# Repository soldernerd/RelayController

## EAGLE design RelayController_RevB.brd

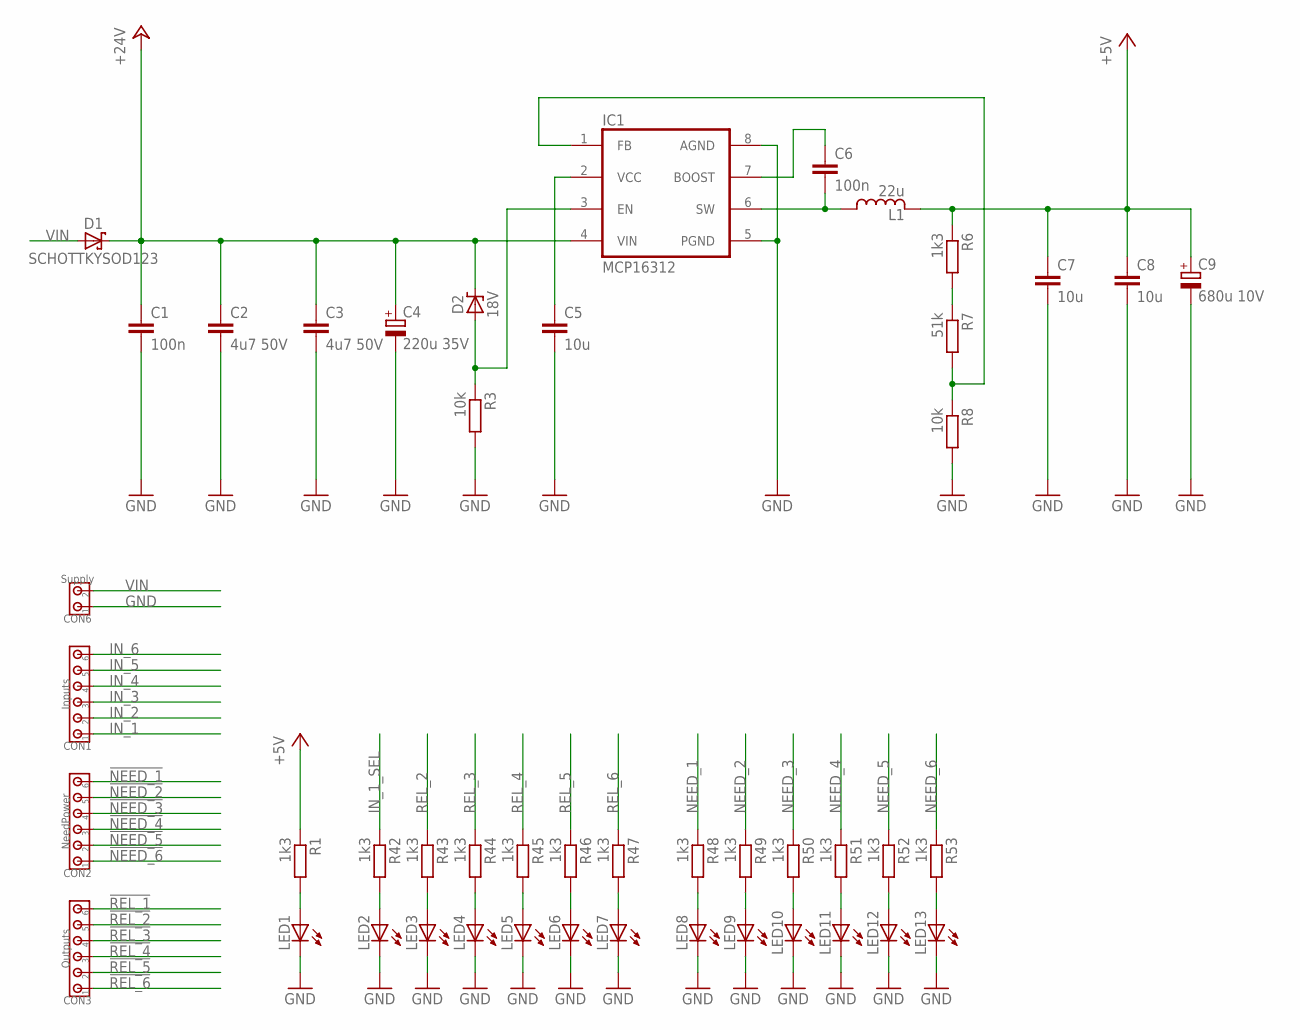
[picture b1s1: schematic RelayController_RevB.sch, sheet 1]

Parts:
C1, C6: 100n; C0805
C2, C3: 4u7 50V; C1206
C4: 220u 35V; 8MM
C5, C7, C8: 10u; C0805
C9: 680u 10V; 8MM
CON1: Inputs; 3.5MM_6X
CON2: NeedPower; 3.5MM_6X
CON3: Outputs; 3.5MM_6X
CON6: Supply; 3.5MM_2X
D1: SCHOTTKYSOD123; SOD123
D2: 18V; SOD323
IC1: MCP16312; MSOP8
L1: 22u; LPS4018
LED1, LED2, LED3, LED4, LED5, LED6, LED7, LED8, LED9, LED10, LED11, LED12, LED13: LED0805_NB; LED0805_NOBOARDER
R1, R6, R42, R43, R44, R45, R46, R47, R48, R49, R50, R51, R52, R53: 1k3; R0805
R3, R8: 10k; R0805
R7: 51k; R0805

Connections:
!NEED_1!: CON2.6; also elsewhere on the board
!NEED_2!: CON2.5; also elsewhere on the board
!NEED_3!: CON2.4; also elsewhere on the board
!NEED_4!: CON2.3; also elsewhere on the board
!NEED_5!: CON2.2; also elsewhere on the board
!NEED_6!: CON2.1; also elsewhere on the board
!REL_1!: CON3.6; also elsewhere on the board
!REL_2!: CON3.5; also elsewhere on the board
!REL_3!: CON3.4; also elsewhere on the board
!REL_4!: CON3.3; also elsewhere on the board
!REL_5!: CON3.2; also elsewhere on the board
!REL_6!: CON3.1; also elsewhere on the board
+5V: C7.1, C8.1, C9.+, L1.2, R1.1, R6.1; also elsewhere on the board
+24V: C1.1, C2.1, C3.1, C4.+, D1.C, D2.C, IC1.4 (VIN); also elsewhere on the board
BOOST: C6.1, IC1.7 (BOOST)
GND: C1.2, C2.2, C3.2, C4.-, C5.2, C7.2, C8.2, C9.-, CON6.1, IC1.5 (PGND), IC1.8 (AGND), LED1.C, LED2.C, LED3.C, LED4.C, LED5.C, LED6.C, LED7.C, LED8.C, LED9.C, LED10.C, LED11.C, LED12.C, LED13.C, R3.2, R8.2; also elsewhere on the board
IN_1: CON1.1; also elsewhere on the board
IN_1_SEL: R42.1; also elsewhere on the board
IN_2: CON1.2; also elsewhere on the board
IN_3: CON1.3; also elsewhere on the board
IN_4: CON1.4; also elsewhere on the board
IN_5: CON1.5; also elsewhere on the board
IN_6: CON1.6; also elsewhere on the board
unnamed: IC1.1 (FB), R7.2, R8.1
unnamed: LED1.A, R1.2
unnamed: D2.A, IC1.3 (EN), R3.1
unnamed: R6.2, R7.1
unnamed: C5.1, IC1.2 (VCC)
unnamed: LED2.A, R42.2
unnamed: LED3.A, R43.2
unnamed: LED4.A, R44.2
unnamed: LED5.A, R45.2
unnamed: LED6.A, R46.2
unnamed: LED7.A, R47.2
unnamed: LED8.A, R48.2
unnamed: LED9.A, R49.2
unnamed: LED10.A, R50.2
unnamed: LED11.A, R51.2
unnamed: LED12.A, R52.2
unnamed: LED13.A, R53.2
NEED_1: R48.1; also elsewhere on the board
NEED_2: R49.1; also elsewhere on the board
NEED_3: R50.1; also elsewhere on the board
NEED_4: R51.1; also elsewhere on the board
NEED_5: R52.1; also elsewhere on the board
NEED_6: R53.1; also elsewhere on the board
REL_2: R43.1; also elsewhere on the board
REL_3: R44.1; also elsewhere on the board
REL_4: R45.1; also elsewhere on the board
REL_5: R46.1; also elsewhere on the board
REL_6: R47.1; also elsewhere on the board
SWITCH: C6.2, IC1.6 (SW), L1.1
VIN: CON6.2, D1.A

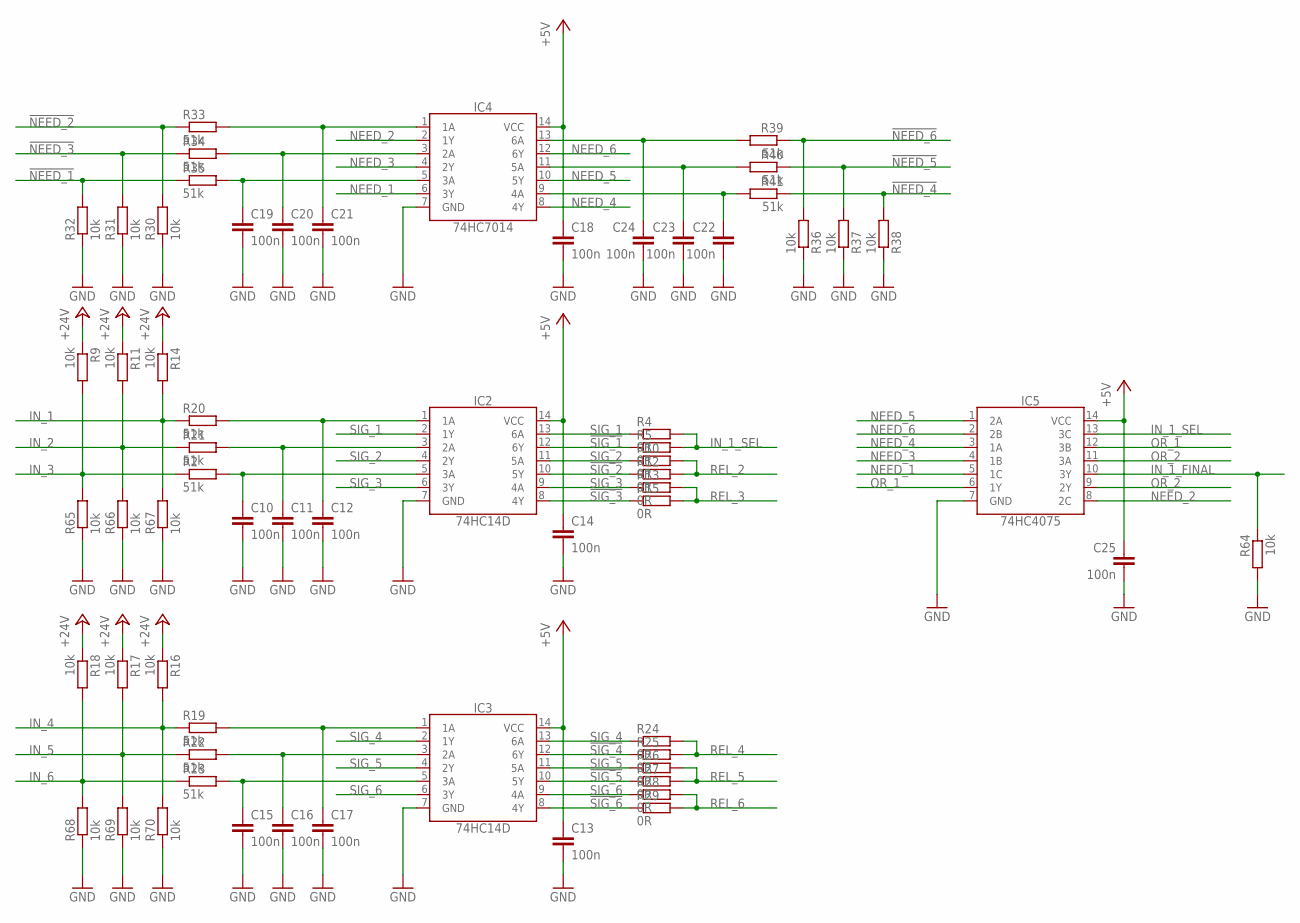
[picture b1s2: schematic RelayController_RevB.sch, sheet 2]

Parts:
C10, C11, C12, C13, C14, C15, C16, C17, C18, C19, C20, C21, C22, C23, C24, C25: 100n; C0805
IC2, IC3: 74HC14D; SO14
IC4: 74HC7014; SO14
IC5: 74HC4075; SO14
R2, R19, R20, R21, R22, R23, R33, R34, R35, R39, R40, R41: 51k; R0805
R4, R5, R10, R12, R13, R15, R24, R25, R26, R27, R28, R29: 0R; R0805
R9, R11, R14, R16, R17, R18, R30, R31, R32, R36, R37, R38, R64, R65, R66, R67, R68, R69, R70: 10k; R0805

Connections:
!NEED_1!: R32.2, R35.1; also elsewhere on the board
!NEED_2!: R30.2, R33.1; also elsewhere on the board
!NEED_3!: R31.2, R34.1; also elsewhere on the board
!NEED_4!: R38.2, R41.1; also elsewhere on the board
!NEED_5!: R37.2, R40.1; also elsewhere on the board
!NEED_6!: R36.2, R39.1; also elsewhere on the board
!SIG_1!: IC2.12 (6Y), R5.1
!SIG_2!: IC2.10 (5Y), R12.1
!SIG_3!: IC2.8 (4Y), R15.1
!SIG_4!: IC3.12 (6Y), R25.1
!SIG_5!: IC3.10 (5Y), R27.1
!SIG_6!: IC3.8 (4Y), R29.1
+5V: C13.1, C14.1, C18.1, C25.1, IC2.14 (VCC), IC3.14 (VCC), IC4.14 (VCC), IC5.14 (VCC); also elsewhere on the board
+24V: R9.1, R11.1, R14.1, R16.1, R17.1, R18.1; also elsewhere on the board
FOO: C10.1, IC2.5 (3A), R2.2
FOO1: C15.1, IC3.5 (3A), R23.2
GND: C10.2, C11.2, C12.2, C13.2, C14.2, C15.2, C16.2, C17.2, C18.2, C19.2, C20.2, C21.2, C22.2, C23.2, C24.2, C25.2, IC2.7 (GND), IC3.7 (GND), IC4.7 (GND), IC5.7 (GND), R30.1, R31.1, R32.1, R36.1, R37.1, R38.1, R64.2, R65.1, R66.1, R67.1, R68.1, R69.1, R70.1; also elsewhere on the board
IN_1: R14.2, R20.1, R67.2; also elsewhere on the board
IN_1_FINAL: IC5.10 (3Y), R64.1; also elsewhere on the board
IN_1_SEL: IC5.13 (3C), R4.2, R5.2; also elsewhere on the board
IN_2: R11.2, R21.1, R66.2; also elsewhere on the board
IN_3: R2.1, R9.2, R65.2; also elsewhere on the board
IN_4: R16.2, R19.1, R70.2; also elsewhere on the board
IN_5: R17.2, R22.1, R69.2; also elsewhere on the board
IN_6: R18.2, R23.1, R68.2; also elsewhere on the board
unnamed: C17.1, IC3.1 (1A), R19.2
unnamed: C16.1, IC3.3 (2A), R22.2
unnamed: C21.1, IC4.1 (1A), R33.2
unnamed: C20.1, IC4.3 (2A), R34.2
unnamed: C24.1, IC4.13 (6A), R39.2
unnamed: C23.1, IC4.11 (5A), R40.2
unnamed: C22.1, IC4.9 (4A), R41.2
unnamed: C12.1, IC2.1 (1A), R20.2
unnamed: C11.1, IC2.3 (2A), R21.2
unnamed: C19.1, IC4.5 (3A), R35.2
NEED_1: IC4.6 (3Y), IC5.5 (1C); also elsewhere on the board
NEED_2: IC4.2 (1Y), IC5.8 (2C); also elsewhere on the board
NEED_3: IC4.4 (2Y), IC5.4 (1B); also elsewhere on the board
NEED_4: IC4.8 (4Y), IC5.3 (1A); also elsewhere on the board
NEED_5: IC4.10 (5Y), IC5.1 (2A); also elsewhere on the board
NEED_6: IC4.12 (6Y), IC5.2 (2B); also elsewhere on the board
OR_1: IC5.6 (1Y), IC5.12 (3B)
OR_2: IC5.9 (2Y), IC5.11 (3A)
REL_2: R10.2, R12.2; also elsewhere on the board
REL_3: R13.2, R15.2; also elsewhere on the board
REL_4: R24.2, R25.2; also elsewhere on the board
REL_5: R26.2, R27.2; also elsewhere on the board
REL_6: R28.2, R29.2; also elsewhere on the board
SIG_1: IC2.2 (1Y), IC2.13 (6A), R4.1
SIG_2: IC2.4 (2Y), IC2.11 (5A), R10.1
SIG_3: IC2.6 (3Y), IC2.9 (4A), R13.1
SIG_4: IC3.2 (1Y), IC3.13 (6A), R24.1
SIG_5: IC3.4 (2Y), IC3.11 (5A), R26.1
SIG_6: IC3.6 (3Y), IC3.9 (4A), R28.1

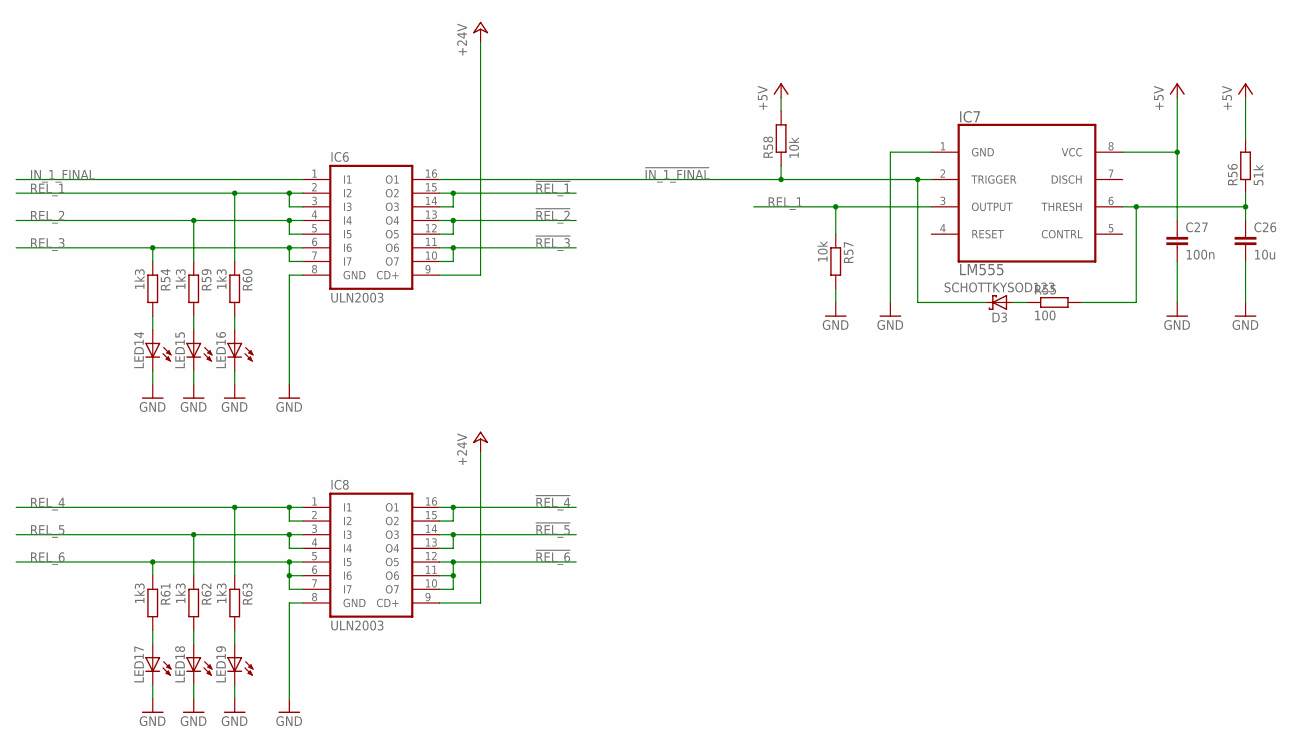
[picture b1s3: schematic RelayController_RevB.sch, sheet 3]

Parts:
C26: 10u; C0805
C27: 100n; C0805
D3: SCHOTTKYSOD123; SOD123
IC6, IC8: ULN2003; SO16
IC7: LM555; SOIC8
LED14, LED15, LED16, LED17, LED18, LED19: LED0805_NB; LED0805_NOBOARDER
R54, R59, R60, R61, R62, R63: 1k3; R0805
R55: 100; R0805
R56: 51k; R0805
R57, R58: 10k; R0805

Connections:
!IN_1_FINAL!: D3.C, IC6.16 (O1), IC7.2 (TRIGGER), R58.1
!REL_1!: IC6.14 (O3), IC6.15 (O2); also elsewhere on the board
!REL_2!: IC6.12 (O5), IC6.13 (O4); also elsewhere on the board
!REL_3!: IC6.10 (O7), IC6.11 (O6); also elsewhere on the board
!REL_4!: IC8.15 (O2), IC8.16 (O1); also elsewhere on the board
!REL_5!: IC8.13 (O4), IC8.14 (O3); also elsewhere on the board
!REL_6!: IC8.10 (O7), IC8.11 (O6), IC8.12 (O5); also elsewhere on the board
+5V: C27.1, IC7.8 (VCC), R56.2, R58.2; also elsewhere on the board
+24V: IC6.9 (CD+), IC8.9 (CD+); also elsewhere on the board
GND: C26.2, C27.2, IC6.8 (GND), IC7.1 (GND), IC8.8 (GND), LED14.C, LED15.C, LED16.C, LED17.C, LED18.C, LED19.C, R57.2; also elsewhere on the board
IN_1_FINAL: IC6.1 (I1); also elsewhere on the board
unnamed: C26.1, IC7.6 (THRESH), R55.2, R56.1
unnamed: D3.A, R55.1
unnamed: LED14.A, R54.2
unnamed: LED15.A, R59.2
unnamed: LED16.A, R60.2
unnamed: LED17.A, R61.2
unnamed: LED18.A, R62.2
unnamed: LED19.A, R63.2
REL_1: IC6.2 (I2), IC6.3 (I3), IC7.3 (OUTPUT), R57.1, R60.1
REL_2: IC6.4 (I4), IC6.5 (I5), R59.1; also elsewhere on the board
REL_3: IC6.6 (I6), IC6.7 (I7), R54.1; also elsewhere on the board
REL_4: IC8.1 (I1), IC8.2 (I2), R63.1; also elsewhere on the board
REL_5: IC8.3 (I3), IC8.4 (I4), R62.1; also elsewhere on the board
REL_6: IC8.5 (I5), IC8.6 (I6), IC8.7 (I7), R61.1; also elsewhere on the board

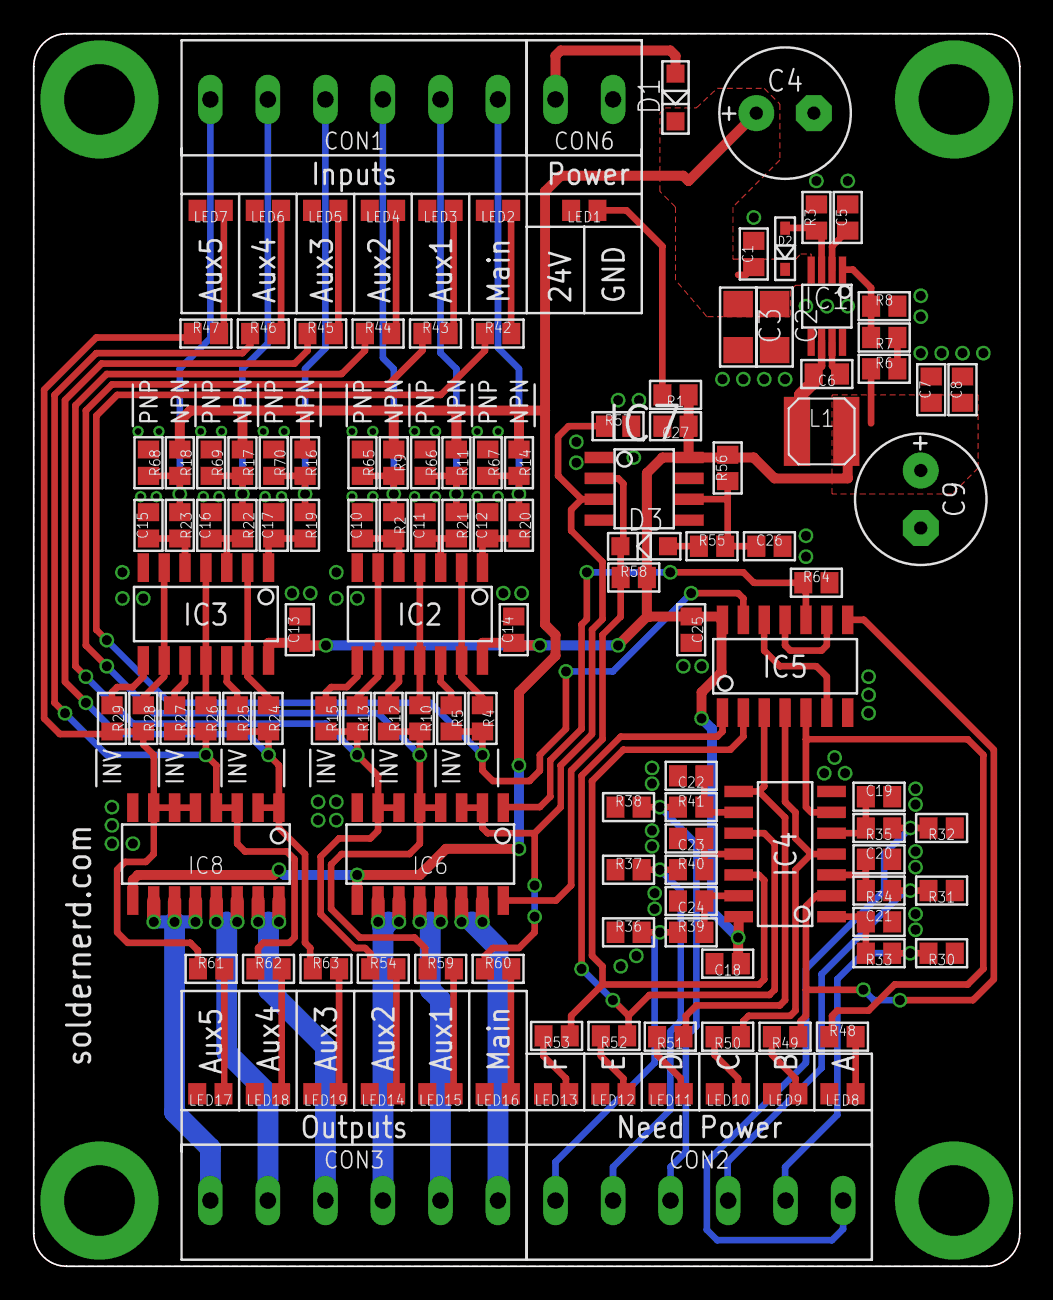
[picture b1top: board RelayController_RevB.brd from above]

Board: 2 copper layers, 60.0 x 75.0 mm, 132 parts (0 on the bottom side), 90 nets.

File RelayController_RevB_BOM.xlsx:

Relay Controller Rev B BOM
Qty | Description | Value | Device | Package | Parts
1 | 8-pin header | Inputs | CON_6X3.5MM | 3.5MM_6X | CON1
1 | 12-pin header | NeedPower | CON_6X3.5MM | 3.5MM_6X | CON2
1 | Capacitor | 220u 35V | C_POLARIZED8MM | 8MM | C4
1 | Capacitor | 680u 10V | C_POLARIZED8MM | 8MM | C9
2 | Capacitor | 4u7 50V | CC1206 | C1206 | C2, C3
4 | Capacitor | 10u | CC0805 | C0805 | C5, C7, C8, C26
19 | Capacitor | 100n | CC0805 | C0805 | C1, C6, C10, C11, C12, C13, C14, C15, C16, C17, C18, C19, C20, C21, C22, C23, C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
1 | LED green |  | LED0805_NB | LED0805_NOBOARDER | LED1
18 | LED orange |  | LED0805_NB | LED0805_NOBOARDER | LED2, LED3, LED4, LED5, LED6, LED7, LED8, LED9, LED10, LED11, LED12, LED13, LED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
1 | Inductor | 22u | INDUCTORLPS4018 | LPS4018 | L1
1 | Voltage regulator | MCP16312 | MCP16311 | MSOP8 | IC1
6 | RESISTOR, European symbol | 0R | RESISTORR0805 | R0805 | R4, R5, R10, R12, R13, R15, R24, R25, R26, R27, R28, R29
1 | RESISTOR, European symbol | 100R | RESISTORR0805 | R0805 | R55
17 | RESISTOR, European symbol | 10k | RESISTORR0805 | R0805 | R3, R8, R9, R11, R14, R16, R17, R18, R30, R31, R32, R36, R37, R38, R57, R58, R6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
20 | RESISTOR, European symbol | 1k3 | RESISTORR0805 | R0805 | R1, R6, R48, R49, R50, R51, R52, R53, R54, R59, R60, R61, R62, R63
14 | RESISTOR, European symbol | 51k | RESISTORR0805 | R0805 | R2, R7, R19, R20, R21, R22, R23, R33, R34, R35, R39, R40, R41, R56
2 | Hex Inverter Schmitt Trigger | 74HC14D | 74HC14D | SO14 | IC2, IC3
1 | Triple 3-input OR gate | 74HC4075 | 74HC4075 | SO14 | IC5
1 | Hex non-inverting precision Schmitt-trigger | 74HC7014 | 74HC7014 | SO14 | IC4
2 | Seven Darlington array | TPL7407 | TPL7407 | SO16 | IC6, IC8
2 |  | SCHOTTKYSOD123 | SCHOTTKYSOD123 | SOD123 | D1, D3
1 |  | 18V | ZENERSOD323 | SOD323 | D2
1 |  | LM555 | LM555 | SOIC8 | IC7

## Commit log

2020-12-08 Initial commit but fully functional
